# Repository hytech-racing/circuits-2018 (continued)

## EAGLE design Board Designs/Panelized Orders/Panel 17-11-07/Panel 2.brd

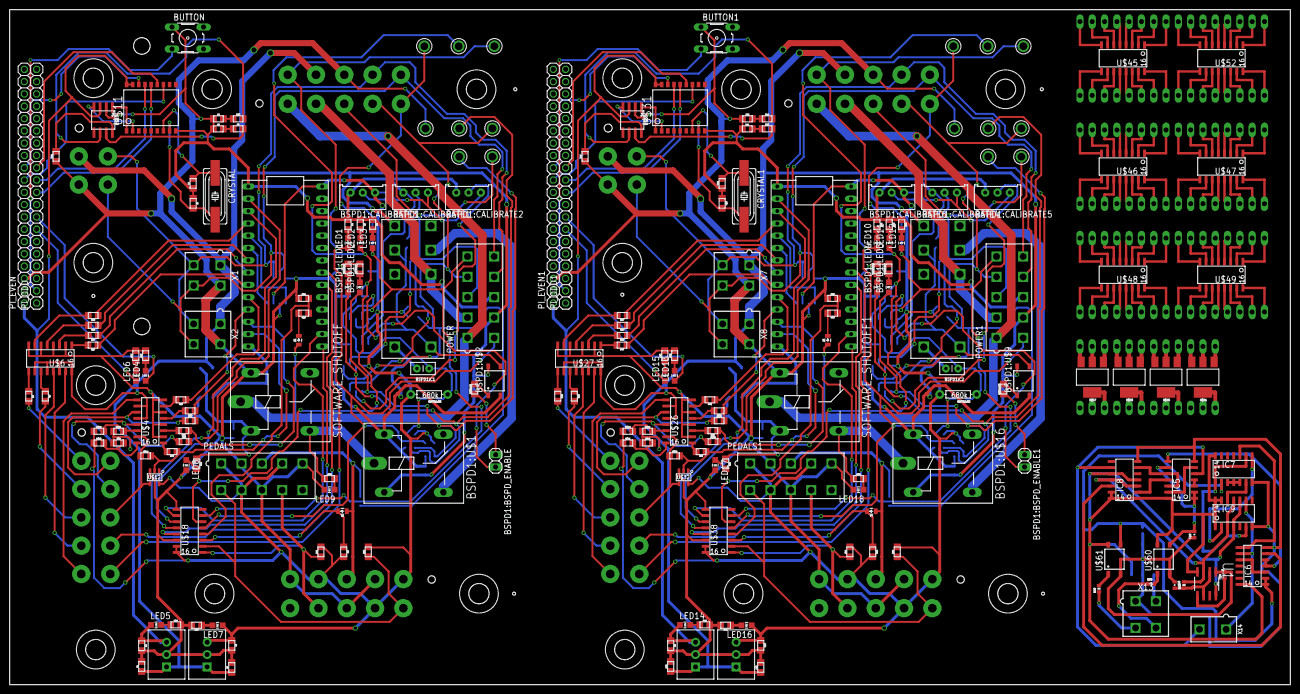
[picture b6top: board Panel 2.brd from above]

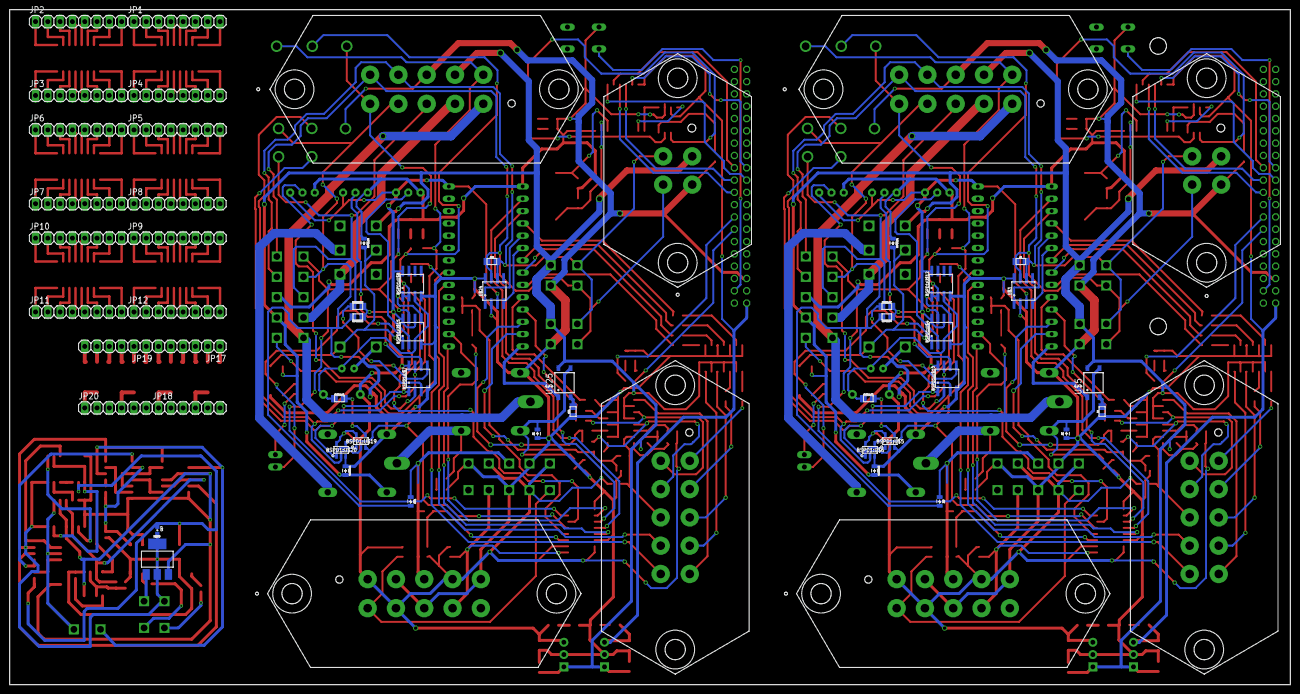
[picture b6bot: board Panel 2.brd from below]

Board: 2 copper layers, 264.4 x 139.4 mm, 270 parts (58 on the bottom side), 336 nets.

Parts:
BSPD1:BSPD_ENABLE, BSPD1:BSPD_ENABLE1: JUMPER; 1X02
BSPD1:C1, BSPD1:C2: .47u; CAP-PTH-SMALLEZ
BSPD1:CALIBRATE1, BSPD1:CALIBRATE2, BSPD1:CALIBRATE3, BSPD1:CALIBRATE4, BSPD1:CALIBRATE5, BSPD1:CALIBRATE6: TRIMPOT_3296
BSPD1:D1, BSPD1:D2, BSPD1:D3, BSPD1:D4: DIODE0805; 0805_D
BSPD1:LED1, BSPD1:LED4: RED; LED-805
BSPD1:LED2, BSPD1:LED3: YELLOW; LED-805
BSPD1:R1, BSPD1:R3: 330; 0805
BSPD1:R2, BSPD1:R5: 680k; AXIAL-0.3EZ
BSPD1:R4, BSPD1:R7, BSPD1:R11, BSPD1:R12: 10k; 0805
BSPD1:R6, BSPD1:R10: 680; 0805
BSPD1:R8, BSPD1:R9, BSPD1:R13, BSPD1:R14: 270; 0805
BSPD1:U$1, BSPD1:U$16: G5LE; ZF112
BSPD1:U$2, BSPD1:U$9: CPC1002N; SOP04
BSPD1:U$3, BSPD1:U$14: JW2SN-DC12V; JW2SN
BSPD1:U$4, BSPD1:U$7, BSPD1:U$10, BSPD1:U$15: MCP6542SOIC; SOIC-08
BSPD1:U$5, BSPD1:U$19: SN74AHC1G09; SOT-23-5
BSPD1:U$6, BSPD1:U$20: SN74LVC1G08; SOT-23-5
BSPD1:U$8, BSPD1:U$12: MCP6002SOIC; SOIC-08
BSPD1:U$11, BSPD1:U$13, BSPD1:U$17, BSPD1:U$18: TEST_POINT
BUTTON, BUTTON1: B3F-10XX
C1, C2, C5, C8, C9, C10, C15, C16: 10uF; 0805
C3, C4, C11, C12: 560pF; 0805
C6, C7, C13, C14: 22pF; 0805
C17, C18: 0402-CAP
C19, C20: 10nF; 0402-CAP
CRYSTAL, CRYSTAL1: 16MHz; HC49UP
D1, D2, D3, D4, D5, D6: DIODE0805; 0805_D
IC1, IC2, IC3, IC4: TO-220
IC5, IC6, IC7: SN74AHC00D; SOIC-14
IC8, IC9: SN74AHC74D; SOIC-14
JMP, JMP1: DIODE0805; 0805_D
JP1, JP2, JP3, JP4, JP5, JP6, JP7, JP8, JP9, JP10, JP11, JP12: 1X08
JP17, JP18, JP19, JP20: 1X06
LED1, LED6, LED8, LED9, LED10, LED15, LED17, LED18: RED; LED-805
LED2, LED11: YELLOW; LED-805
LED3, LED4, LED12, LED13: GREEN; LED-805
LED5, LED7, LED14, LED16: PURPLE; LED-805
PEDALS, PEDALS1: MINIFIT_5566-10
PI_EVEN, PI_EVEN1: 1X20
PI_ODD, PI_ODD1: 1X20
POWER, POWER1: MINIFIT_5566-10
R1, R30: 120; 0805
R2, R3, R15, R16, R17, R18, R19, R20, R21, R22, R27, R31, R32, R37, R38, R39, R40, R41, R42, R43, R44, R50: 270; 0805
R4, R25, R26, R28, R33, R48, R49, R51: 200; 0805
R5, R23, R45, R46: 100; 0805
R6, R34: 330; 0805
R7, R8, R52, R53: 0; 0805
R9, R10, R11, R54, R55, R56: 10k; 0805
R12, R29, R57, R58: 1.2K; 0805
R13, R35: 43k; 0805
R14, R36: 12k; 0805
R24, R47: 4.7k; 0805
R59, R60: 680Ω; 0402-RES
R61: 100kΩ; 0402-RES
SOFTWARE_SHUTOFF, SOFTWARE_SHUTOFF1: G5LE; ZF112
U1: SA555D; SOIC127P600X175-8N
U$1, U$23: TEENSY_3.2_SIMPLE
U$2, U$13, U$14, U$15, U$16, U$17, U$33, U$34, U$35, U$36, U$37, U$44: TEST_POINT
U$3, U$10, U$24, U$30: MCP2551; SOIC-08
U$4, U$6, U$26, U$27: TLP291-4; SOIC-16
U$5, U$25, U$60, U$61: CPC1002N; SOP04
U$7, U$8, U$9, U$19, U$20, U$21, U$22, U$28, U$29, U$39, U$40, U$41, U$42, U$43: JUMPER; 0805
U$11, U$31: MCP2515SMD; SOIC-18W
U$12, U$32: SN74LV1T34; SOT-23-5
U$18, U$38: MCP3208SOIC; SOIC-16
U$45, U$46, U$47, U$48, U$49, U$52: SOIC16; SOIC-16
U$50, U$51, U$57, U$58: SOT223
U$59: SOT223
X1, X2, X7, X8, X13: CONNECTOR-4; MINIFIT_5566-4
X3, X9: CONNECTOR-4MX150L_VERTICAL-4; MX150L_VERTICAL-4
X4, X5, X6, X10, X11, X12: CONNECTOR-10MX150L_VERTICAL-10; MX150L_VERTICAL-10
X14: CONNECTOR-2; MINIFIT_5566-2

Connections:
12V: U$59.1, X13.2
+5V: BSPD1:CALIBRATE1.1, BSPD1:CALIBRATE2.1, BSPD1:CALIBRATE3.1, BSPD1:R4.1, BSPD1:R5.P$2, BSPD1:R7.2, BSPD1:U$4.6, BSPD1:U$4.8, BSPD1:U$5.5, BSPD1:U$6.5, BSPD1:U$10.8, BSPD1:U$12.8, C8.1, IC3.3, LED7.A, PEDALS.1, PEDALS.4, PEDALS.7, R9.2, R10.2, R11.2, U$1.VIN, U$3.3, U$12.5, U$18.15, U$18.16, U$20.1, U$22.1, X4.1, X4.4, X4.7
+5V1: BSPD1:CALIBRATE4.1, BSPD1:CALIBRATE5.1, BSPD1:CALIBRATE6.1, BSPD1:R2.P$2, BSPD1:R11.1, BSPD1:R12.2, BSPD1:U$7.8, BSPD1:U$8.8, BSPD1:U$15.6, BSPD1:U$15.8, BSPD1:U$19.5, BSPD1:U$20.5, C16.1, IC4.3, LED16.A, PEDALS1.1, PEDALS1.4, PEDALS1.7, R54.2, R55.2, R56.2, U$23.VIN, U$24.3, U$32.5, U$38.15, U$38.16, U$41.1, U$43.1, X10.1, X10.4, X10.7
+5V2: IC5.14, IC6.14, IC7.14, IC8.1, IC8.4, IC8.10, IC8.13, IC8.14, IC9.1, IC9.4, IC9.10, IC9.13, IC9.14, U1.4, U1.8, U$59.3, U$60.4, U$61.4
+5V/1: C2.1, IC2.3, LED5.A, PI_EVEN.1, U$10.3, U$11.17, U$11.18
+5V/2: C9.1, IC1.3, LED14.A, PI_EVEN1.1, U$30.3, U$31.17, U$31.18
+12V: BSPD1:D2.C, BSPD1:U$1.2, BSPD1:U$2.4, BSPD1:U$3.4, C1.1, C5.1, IC2.1, IC3.1, POWER.7, U$4.10, U$4.12, U$5.4, U$6.10, U$6.12, U$6.14, U$6.16, U$9.1, U$21.1, X1.1, X2.1, X3.1, X5.7
+12V1: BSPD1:D4.C, BSPD1:U$9.4, BSPD1:U$14.4, BSPD1:U$16.2, C10.1, C15.1, IC1.1, IC4.1, POWER1.7, U$25.4, U$26.10, U$26.12, U$27.10, U$27.12, U$27.14, U$27.16, U$40.1, U$42.1, X7.1, X8.1, X9.1, X11.7
BMS_5V: C17.1, IC6.1, IC6.2, IC7.2, U$61.3
BMS_IN: R60.2, U$61.1
BMS_OUT: IC6.9, IC9.9, X14.1
BSPD1:N$1: BSPD1:D1.C, BSPD1:U$2.3, BSPD1:U$3.3, BSPD1:U$3.COIL-, BSPD1:U$4.5
BSPD1:N$2: BSPD1:R3.2, BSPD1:U$5.4
BSPD1:N$3: BSPD1:R6.2, BSPD1:U$2.1
BSPD1:N$4: BSPD1:BSPD_ENABLE.1, BSPD1:R6.1
BSPD1:N$5: BSPD1:CALIBRATE2.2, BSPD1:U$10.2
BSPD1:N$6: BSPD1:CALIBRATE1.2, BSPD1:U$10.6
BSPD1:N$7: BSPD1:CALIBRATE3.2, BSPD1:U$4.2
BSPD1:N$8: BSPD1:BSPD_ENABLE.2, BSPD1:U$4.1
BSPD1:N$9: BSPD1:C2.1, BSPD1:R1.1, BSPD1:R2.P$1, BSPD1:U$8.3, BSPD1:U$15.3
BSPD1:N$10: BSPD1:CALIBRATE6.2, BSPD1:U$15.2
BSPD1:N$11: BSPD1:D3.C, BSPD1:U$9.3, BSPD1:U$14.3, BSPD1:U$14.COIL-, BSPD1:U$15.5
BSPD1:N$12: BSPD1:R1.2, BSPD1:U$19.4
BSPD1:N$13: BSPD1:C1.1, BSPD1:R3.1, BSPD1:R5.P$1, BSPD1:U$4.3, BSPD1:U$12.3
BSPD1:N$14: BSPD1:LED2.C, BSPD1:R8.1
BSPD1:N$15: BSPD1:LED1.C, BSPD1:R9.1
BSPD1:N$16: BSPD1:LED1.A, BSPD1:U$5.2, BSPD1:U$6.2, BSPD1:U$10.7, BSPD1:U$11.P$1
BSPD1:N$17: BSPD1:LED2.A, BSPD1:U$5.1, BSPD1:U$6.1, BSPD1:U$10.1, BSPD1:U$13.P$1
BSPD1:N$18: BSPD1:R10.2, BSPD1:U$9.1
BSPD1:N$19: BSPD1:LED4.C, BSPD1:R14.1
BSPD1:N$20: BSPD1:LED3.C, BSPD1:R13.1
BSPD1:N$21: BSPD1:LED4.A, BSPD1:U$7.7, BSPD1:U$17.P$1, BSPD1:U$19.2, BSPD1:U$20.2
BSPD1:N$22: BSPD1:LED3.A, BSPD1:U$7.1, BSPD1:U$18.P$1, BSPD1:U$19.1, BSPD1:U$20.1
BSPD1:N$23: BSPD1:BSPD_ENABLE1.1, BSPD1:R10.1
BSPD1:N$24: BSPD1:BSPD_ENABLE1.2, BSPD1:U$15.1
BSPD1:N$25: BSPD1:CALIBRATE5.2, BSPD1:U$7.2
BSPD1:N$26: BSPD1:CALIBRATE4.2, BSPD1:U$7.6
BSPD1:SHUTDOWN_C: BSPD1:U$1.S, BSPD1:U$3.6
BSPD1:SHUTDOWN_C1: BSPD1:U$14.6, BSPD1:U$16.S
BUT: BUTTON.3, PI_ODD.2
BUT1: BUTTON1.3, PI_ODD1.2
CAN-H: R5.2, U$10.7
CAN-H1: R45.2, U$30.7
CAN-L: R23.2, U$10.6
CAN-L1: R46.2, U$30.6
CANH: POWER.10, R1.1, U$3.7, X1.4, X2.4, X3.4, X5.10
CANH1: POWER1.10, R30.1, U$24.7, X7.4, X8.4, X9.4, X11.10
CANL: POWER.9, R1.2, U$3.6, X1.3, X2.3, X3.3, X5.9
CANL1: POWER1.9, R30.2, U$24.6, X7.3, X8.3, X9.3, X11.9
CS: PI_EVEN.12, U$11.16
CS1: PI_EVEN1.12, U$31.16
DASH_CTRL1: R15.1, U$1.D2
DASH_CTRL2: R16.1, U$1.D5
DASH_CTRL3: R17.1, U$1.D6
DASH_CTRL4: R18.1, U$1.D7(RX3)
DASH_CTRL5: R19.1, U$1.D8(TX3)
DASH_CTRL6: R20.1, U$1.D9(RX2), U$7.2
DASH_CTRL7: R21.1, U$1.D10(TX2), U$8.2
DASH_CTRL8: R22.1, U$1.D11, U$12.2, U$19.2
DASH_CTRL9: U$1.A4, X6.9
DASH_CTRL10: U$1.A5, X6.10
DASH_CTRL11: R38.1, U$23.D5
DASH_CTRL12: R39.1, U$23.D6
DASH_CTRL13: R40.1, U$23.D7(RX3)
DASH_CTRL14: R42.1, U$23.D9(RX2), U$28.2
DASH_CTRL15: R44.1, U$23.D11, U$32.2, U$39.2
DASH_CTRL16: U$23.A5, X12.10
DASH_CTRL17: R37.1, U$23.D2
DASH_CTRL18: R41.1, U$23.D8(TX3)
DASH_CTRL19: R43.1, U$23.D10(TX2), U$29.2
DASH_CTRL20: U$23.A4, X12.9
DASH_IO1: R7.2, X6.1
DASH_IO2: R8.2, X6.2
DASH_IO3: U$6.13, X6.3
DASH_IO4: U$6.15, X6.4
DASH_IO5: U$4.9, X6.5
DASH_IO6: U$4.11, U$7.1, X6.6
DASH_IO7: U$4.13, U$8.1, X6.7
DASH_IO8: U$4.15, U$12.4, U$19.1, X6.8
DASH_IO9: R52.2, X12.1
DASH_IO10: R53.2, X12.2
DASH_IO11: U$27.13, X12.3
DASH_IO12: U$27.15, X12.4
DASH_IO13: U$26.9, X12.5
DASH_IO14: U$26.11, U$28.1, X12.6
DASH_IO15: U$26.13, U$29.1, X12.7
DASH_IO16: U$26.15, U$32.4, U$39.1, X12.8
GND: BSPD1:C1.2, BSPD1:CALIBRATE1.3, BSPD1:CALIBRATE2.3, BSPD1:CALIBRATE3.3, BSPD1:D1.A, BSPD1:D2.A, BSPD1:R8.2, BSPD1:R9.2, BSPD1:U$1.1, BSPD1:U$2.2, BSPD1:U$3.COIL+, BSPD1:U$4.4, BSPD1:U$5.3, BSPD1:U$6.3, BSPD1:U$10.4, BSPD1:U$12.4, BUTTON.1, C1.2, C2.2, C3.1, C4.1, C5.2, C6.1, C7.1, C8.2, D3.A, IC2.2, IC3.2, LED8.C, LED9.C, PEDALS.2, PEDALS.5, PEDALS.8, PI_EVEN.3, POWER.8, R2.1, R3.1, R4.1, R6.1, R14.1, R24.1, R25.2, R26.2, R27.2, R28.2, SOFTWARE_SHUTOFF.1, U$1.GND, U$2.P$1, U$3.2, U$3.8, U$4.2, U$4.4, U$4.6, U$4.8, U$6.2, U$6.4, U$6.6, U$6.8, U$10.2, U$11.9, U$12.3, U$18.9, U$18.14, X1.2, X2.2, X3.2, X4.2, X4.5, X4.8, X5.8
GND1: BSPD1:C2.2, BSPD1:CALIBRATE4.3, BSPD1:CALIBRATE5.3, BSPD1:CALIBRATE6.3, BSPD1:D3.A, BSPD1:D4.A, BSPD1:R13.2, BSPD1:R14.2, BSPD1:U$7.4, BSPD1:U$8.4, BSPD1:U$9.2, BSPD1:U$14.COIL+, BSPD1:U$15.4, BSPD1:U$16.1, BSPD1:U$19.3, BSPD1:U$20.3, BUTTON1.1, C9.2, C10.2, C11.1, C12.1, C13.1, C14.1, C15.2, C16.2, D6.A, IC1.2, IC4.2, LED17.C, LED18.C, PEDALS1.2, PEDALS1.5, PEDALS1.8, PI_EVEN1.3, POWER1.8, R31.1, R32.1, R33.1, R34.1, R36.1, R47.1, R48.2, R49.2, R50.2, R51.2, SOFTWARE_SHUTOFF1.1, U$23.GND, U$24.2, U$24.8, U$26.2, U$26.4, U$26.6, U$26.8, U$27.2, U$27.4, U$27.6, U$27.8, U$30.2, U$31.9, U$32.3, U$38.9, U$38.14, U$44.P$1, X7.2, X8.2, X9.2, X10.2, X10.5, X10.8, X11.8
GND2: C17.2, C18.1, C19.2, C20.1, IC5.7, IC6.7, IC7.7, IC8.7, IC9.7, U1.1, U$59.2, U$59.4, U$60.2, U$61.2, X13.1
IMD_5V: C18.2, IC5.1, IC5.2, IC5.9, U$60.3
IMD_IN: R59.2, U$60.1
IMD_OUT: IC5.5, IC8.9, X14.2
INT: PI_EVEN.11, U$11.12
INT1: PI_EVEN1.11, U$31.12
LED1: LED4.A, PI_ODD.8
LED2: LED6.A, PI_ODD.7
LED3: LED15.A, PI_ODD1.7
LED4: LED13.A, PI_ODD1.8
MCP3208_CS: U$1.A0, U$18.10
MCP3208_CS1: U$23.A0, U$38.10
MCP3208_DIN: U$1.D1(TX1), U$18.11
MCP3208_DIN1: U$23.D1(TX1), U$38.11
MCP3208_DOUT: U$1.D0(RX1), U$18.12
MCP3208_DOUT1: U$23.D0(RX1), U$38.12
MCP3208_SCK: U$1.D13, U$18.13
MCP3208_SCK1: U$23.D13, U$38.13
MISO: PI_ODD.11, U$11.15
MISO1: PI_ODD1.11, U$31.15
MOSI: PI_ODD.10, U$11.14
MOSI1: PI_ODD1.10, U$31.14
unnamed: R7.1, U$6.9
unnamed: U$1.D4(CANRX), U$3.4
unnamed: R8.1, U$6.11
unnamed: U$4.16, U$9.2, U$20.2
unnamed: U$1.D3(CANTX), U$3.1
unnamed: U$4.14, U$21.2, U$22.2
unnamed: D1.C, R9.1, U$18.3
unnamed: LED8.A, R12.2
unnamed: LED9.A, R29.2
unnamed: U$23.D4(CANRX), U$24.4
unnamed: U$23.D3(CANTX), U$24.1
unnamed: D3.C, R12.1, SOFTWARE_SHUTOFF.2, U$5.3
unnamed: D2.C, R13.2
unnamed: LED1.C, R2.2
unnamed: LED2.C, R3.2
unnamed: LED3.C, R4.2
unnamed: LED10.C, R31.2
unnamed: LED11.C, R32.2
unnamed: R15.2, U$6.7
unnamed: LED12.C, R33.2
unnamed: R34.2, U$25.2
unnamed: R6.2, U$5.2
unnamed: D4.C, R54.1, U$38.3
unnamed: R16.2, U$6.5
unnamed: D6.C, R57.1, SOFTWARE_SHUTOFF1.2, U$25.3
unnamed: D5.C, R35.2
unnamed: R21.2, U$4.3
unnamed: R17.2, U$6.3
unnamed: R18.2, U$6.1
unnamed: R37.2, U$27.7
unnamed: R19.2, U$4.7
unnamed: R20.2, U$4.5
unnamed: R38.2, U$27.5
unnamed: R39.2, U$27.3
unnamed: R22.2, U$4.1
unnamed: R40.2, U$27.1
unnamed: U$10.1, U$11.1
unnamed: R41.2, U$26.7
unnamed: U$10.4, U$11.2
unnamed: C6.2, CRYSTAL.2, U$11.8
unnamed: R24.2, U$10.8
unnamed: C7.2, CRYSTAL.1, U$11.7
unnamed: C3.2, R5.1
unnamed: R42.2, U$26.5
unnamed: R43.2, U$26.3
unnamed: R44.2, U$26.1
unnamed: U$30.1, U$31.1
unnamed: U$30.4, U$31.2
unnamed: C13.2, CRYSTAL1.2, U$31.8
unnamed: C4.2, R23.1
unnamed: R47.2, U$30.8
unnamed: LED4.C, R25.1
unnamed: LED5.C, R26.1
unnamed: LED6.C, R27.1
unnamed: LED7.C, R28.1
unnamed: C14.2, CRYSTAL1.1, U$31.7
unnamed: C11.2, R45.1
unnamed: C12.2, R46.1
unnamed: LED13.C, R48.1
unnamed: LED14.C, R49.1
unnamed: LED15.C, R50.1
unnamed: LED16.C, R51.1
unnamed: R52.1, U$27.9
unnamed: R53.1, U$27.11
unnamed: U$26.16, U$40.2, U$41.2
unnamed: U$26.14, U$42.2, U$43.2
unnamed: LED17.A, R57.2
unnamed: LED18.A, R58.2
unnamed: JP1.1, U$45.1
unnamed: JP1.2, U$45.2
unnamed: JP1.3, U$45.3
unnamed: JP1.4, U$45.4
unnamed: JP1.5, U$45.5
unnamed: JP1.6, U$45.6
unnamed: JP1.7, U$45.7
unnamed: JP1.8, U$45.8
unnamed: JP2.1, U$52.1
unnamed: JP2.2, U$52.2
unnamed: JP2.3, U$52.3
unnamed: JP2.4, U$52.4
unnamed: JP2.5, U$52.5
unnamed: JP2.6, U$52.6
unnamed: JP2.7, U$52.7
unnamed: JP2.8, U$52.8
unnamed: JP3.1, U$52.16
unnamed: JP3.2, U$52.15
unnamed: JP3.3, U$52.14
unnamed: JP3.4, U$52.13
unnamed: JP3.5, U$52.12
unnamed: JP3.6, U$52.11
unnamed: JP3.7, U$52.10
unnamed: JP3.8, U$52.9
unnamed: JP4.1, U$45.16
unnamed: JP4.2, U$45.15
unnamed: JP4.3, U$45.14
unnamed: JP4.4, U$45.13
unnamed: JP4.5, U$45.12
unnamed: JP4.6, U$45.11
unnamed: JP4.7, U$45.10
unnamed: JP4.8, U$45.9
unnamed: JP5.1, U$46.1
unnamed: JP5.2, U$46.2
unnamed: JP5.3, U$46.3
unnamed: JP5.4, U$46.4
unnamed: JP5.5, U$46.5
unnamed: JP5.6, U$46.6
unnamed: JP5.7, U$46.7
unnamed: JP5.8, U$46.8
unnamed: JP6.1, U$47.1
unnamed: JP6.2, U$47.2
unnamed: JP6.3, U$47.3
unnamed: JP6.4, U$47.4
unnamed: JP6.5, U$47.5
unnamed: JP6.6, U$47.6
unnamed: JP6.7, U$47.7
unnamed: JP6.8, U$47.8
unnamed: JP7.1, U$47.16
unnamed: JP7.2, U$47.15
unnamed: JP7.3, U$47.14
unnamed: JP7.4, U$47.13
unnamed: JP7.5, U$47.12
unnamed: JP7.6, U$47.11
unnamed: JP7.7, U$47.10
unnamed: JP7.8, U$47.9
unnamed: JP8.1, U$46.16
unnamed: JP8.2, U$46.15
unnamed: JP8.3, U$46.14
unnamed: JP8.4, U$46.13
unnamed: JP8.5, U$46.12
unnamed: JP8.6, U$46.11
unnamed: JP8.7, U$46.10
unnamed: JP8.8, U$46.9
unnamed: JP9.1, U$48.1
unnamed: JP9.2, U$48.2
unnamed: JP9.3, U$48.3
unnamed: JP9.4, U$48.4
unnamed: JP9.5, U$48.5
unnamed: JP9.6, U$48.6
unnamed: JP9.7, U$48.7
unnamed: JP9.8, U$48.8
unnamed: JP10.1, U$49.1
unnamed: JP10.2, U$49.2
unnamed: JP10.3, U$49.3
unnamed: JP10.4, U$49.4
unnamed: JP10.5, U$49.5
unnamed: JP10.6, U$49.6
unnamed: JP10.7, U$49.7
unnamed: JP10.8, U$49.8
unnamed: JP11.1, U$49.16
unnamed: JP11.2, U$49.15
unnamed: JP11.3, U$49.14
unnamed: JP11.4, U$49.13
unnamed: JP11.5, U$49.12
unnamed: JP11.6, U$49.11
unnamed: JP11.7, U$49.10
unnamed: JP11.8, U$49.9
unnamed: JP12.1, U$48.16
unnamed: JP12.2, U$48.15
unnamed: JP12.3, U$48.14
unnamed: JP12.4, U$48.13
unnamed: JP12.5, U$48.12
unnamed: JP12.6, U$48.11
unnamed: JP12.7, U$48.10
unnamed: JP12.8, U$48.9
unnamed: JP18.1, U$50.4
unnamed: JP17.6, U$50.1
unnamed: JP17.5, U$50.2
unnamed: JP17.4, U$50.3
unnamed: JP17.3, U$57.1
unnamed: JP17.2, U$57.2
unnamed: JP17.1, U$57.3
unnamed: JP18.4, U$57.4
unnamed: JP20.1, U$51.4
unnamed: JP20.4, U$58.4
unnamed: JP19.6, U$51.1
unnamed: JP19.5, U$51.2
unnamed: JP19.4, U$51.3
unnamed: JP19.3, U$58.1
unnamed: JP19.2, U$58.2
unnamed: JP19.1, U$58.3
unnamed: IC5.10, IC5.12, IC8.6
unnamed: IC5.11, IC8.2
unnamed: IC7.1, IC7.9, IC9.6
unnamed: IC7.8, IC9.2
unnamed: IC6.6, IC8.12
unnamed: IC7.6, IC9.12
unnamed: R59.1, X13.4
unnamed: R60.1, X13.3
unnamed: IC5.3, IC5.4
unnamed: IC5.6, IC5.13
unnamed: IC5.8, IC6.4, IC6.5
unnamed: IC6.3, IC6.10
unnamed: IC6.8, IC7.10
unnamed: IC7.3, IC7.4, IC7.5
unnamed: IC8.3, IC8.11, IC9.3, IC9.11, R61.2, U1.3
unnamed: C20.2, R61.1, U1.2, U1.6
unnamed: C19.1, U1.5
RAW_ACCEL1: PEDALS.9, R11.1, U$18.1, X4.9
RAW_ACCEL2: PEDALS.6, R10.1, U$18.2, X4.6
RAW_ACCEL3: PEDALS1.6, R55.1, U$38.2, X10.6
RAW_ACCEL4: PEDALS1.9, R56.1, U$38.1, X10.9
RAW_BRAKE: D1.A, JMP.A, PEDALS.3, X4.3
RAW_BRAKE1: D4.A, JMP1.A, PEDALS1.3, X10.3
READ_CHARGE: BSPD1:U$12.1, BSPD1:U$12.2, LED2.A, U$16.P$1, U$18.6
READ_CHARGE1: BSPD1:U$8.1, BSPD1:U$8.2, LED11.A, U$36.P$1, U$38.6
READ_FAULT: BSPD1:U$4.7, LED3.A, POWER.5, U$15.P$1, U$18.7, X5.5
READ_FAULT1: BSPD1:U$15.7, LED12.A, POWER1.5, U$35.P$1, U$38.7, X11.5
READ_SWITCH: BSPD1:U$6.4, LED1.A, POWER.6, U$17.P$1, U$18.5, X5.6
READ_SWITCH1: BSPD1:U$20.4, LED10.A, POWER1.6, U$37.P$1, U$38.5, X11.6
READ_UPSTREAM_SHUTDOWN: R13.1, R14.2, U$18.4
READ_UPSTREAM_SHUTDOWN1: R35.1, R36.2, U$38.4
SCK: PI_ODD.12, U$11.13
SCK1: PI_ODD1.12, U$31.13
SHUTDOWN_A: D2.A, POWER.1, SOFTWARE_SHUTOFF.P, X5.1
SHUTDOWN_A1: D5.A, POWER1.1, SOFTWARE_SHUTOFF1.P, X11.1
SHUTDOWN_B: BSPD1:U$1.P, R29.1, SOFTWARE_SHUTOFF.S
SHUTDOWN_B1: BSPD1:U$16.P, R58.1, SOFTWARE_SHUTOFF1.S
SHUTDOWN_D: BSPD1:U$3.7, POWER.2, X5.2
SHUTDOWN_D1: BSPD1:U$14.7, POWER1.2, X11.2
SHUTDOWN_RELAY_CTRL: U$1.D12, U$5.1
SHUTDOWN_RELAY_CTRL1: U$23.D12, U$25.1
SIGNAL_BRAKE: BSPD1:R4.2, BSPD1:U$10.5, JMP.C, POWER.4, U$13.P$1, X5.4
SIGNAL_BRAKE1: BSPD1:R11.2, BSPD1:U$7.5, JMP1.C, POWER1.4, U$33.P$1, X11.4
SIGNAL_CURRENT: BSPD1:R7.1, BSPD1:U$10.3, POWER.3, U$14.P$1, X5.3
SIGNAL_CURRENT1: BSPD1:R12.1, BSPD1:U$7.3, POWER1.3, U$34.P$1, X11.3

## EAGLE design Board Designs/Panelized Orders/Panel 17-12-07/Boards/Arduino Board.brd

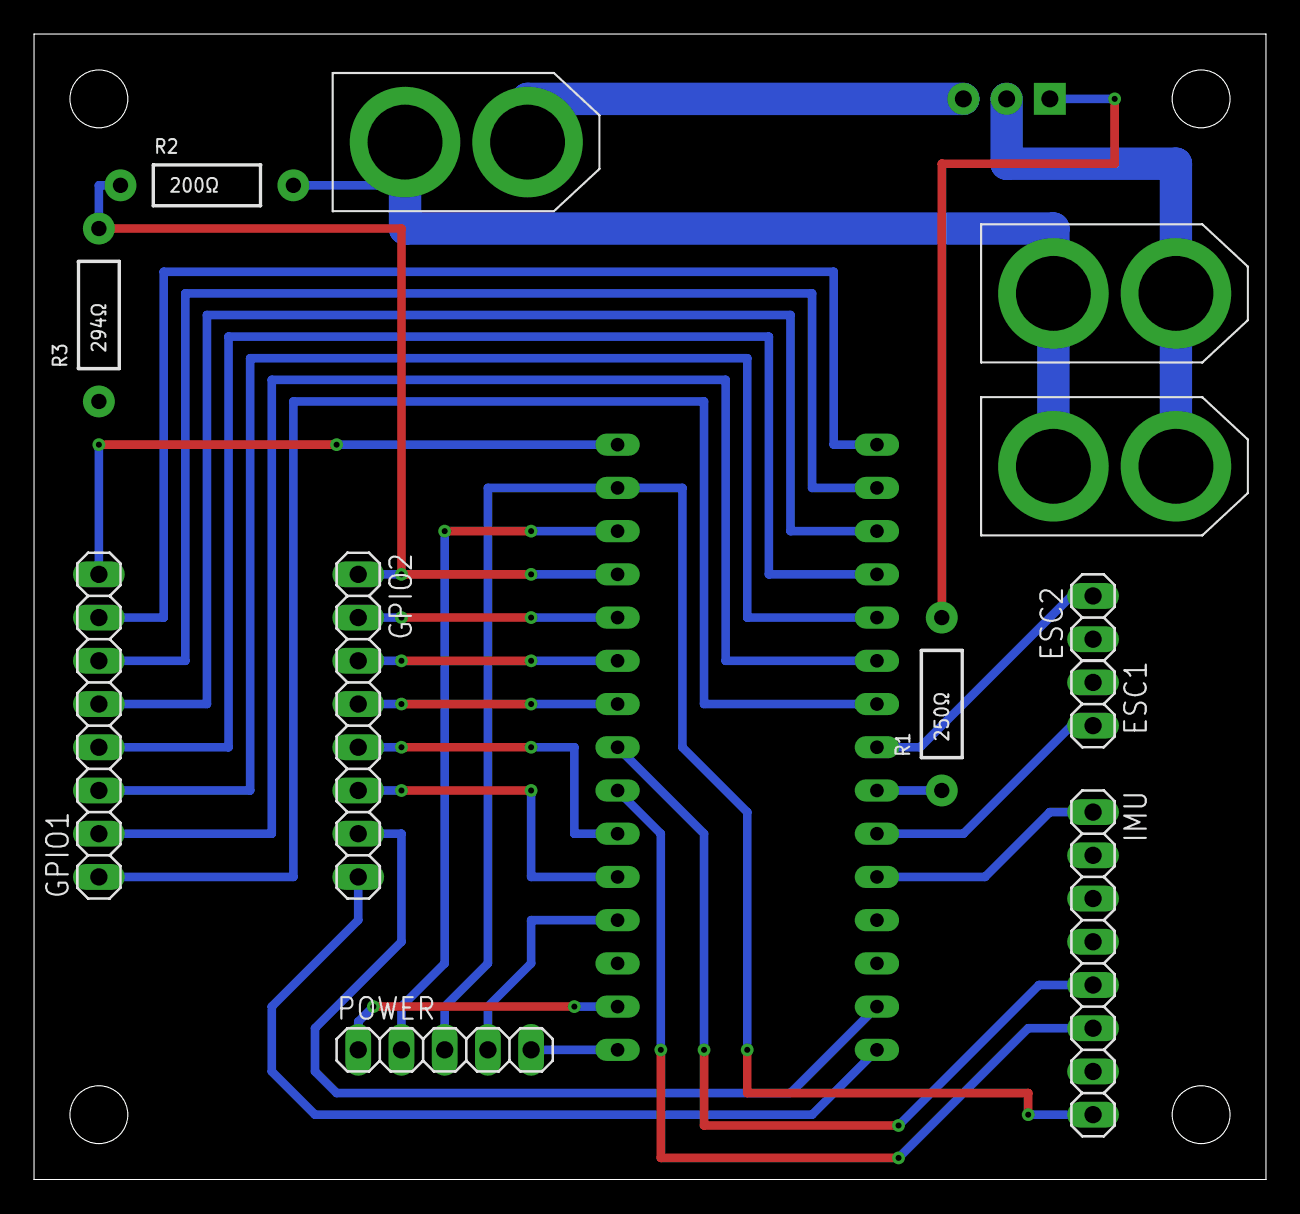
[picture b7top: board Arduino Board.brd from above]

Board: 2 copper layers, 72.4 x 67.3 mm, 14 parts (1 on the bottom side), 30 nets.

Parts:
BATTERY_POWER: XT60
ESC1, ESC2: M02; 1X02
ESC1_POWER, ESC2_POWER: XT60
GPIO1, GPIO2: 1X08
IMU: 1X08
POWER: 1X05
POWER_MOSFET: TO-220-SINK
R1: 250Ω; AXIAL-0.4
R2: 200Ω; AXIAL-0.4
R3: 294Ω; AXIAL-0.4
U$1: ARDUINO_NANO

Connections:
3.3V: IMU.8, POWER.3, U$1.3.3V
5V: POWER.4, U$1.5V
A0: GPIO2.1, R2.P$1, R3.P$2, U$1.A0
A1: GPIO2.2, U$1.A1
A2: GPIO2.3, U$1.A2
A3: GPIO2.4, U$1.A3
A6: GPIO2.5, U$1.A6
A7: GPIO2.6, U$1.A7
AREF: POWER.2, U$1.AREF
D0(RX): GPIO2.7, U$1.D0(RX)
D1(TX): GPIO2.8, U$1.D1(TX)
D6: GPIO1.1, U$1.D6
D7: GPIO1.2, U$1.D7
D8: GPIO1.3, U$1.D8
D9: GPIO1.4, U$1.D9
D10: GPIO1.5, U$1.D10
D11: GPIO1.6, U$1.D11
D12: GPIO1.7, U$1.D12
D13: GPIO1.8, U$1.D13
DRIVE: R1.P$1, U$1.D4
ESC1: ESC1.2, U$1.D3
ESC2: ESC2.2, U$1.D5
GND: BATTERY_POWER.-, ESC1.1, ESC2.1, IMU.7, POWER.1, POWER_MOSFET.3, R3.P$1, U$1.GND, U$1.GND1
INT: IMU.1, U$1.D2
unnamed: POWER_MOSFET.1, R1.P$2
SCL: IMU.6, U$1.A5
SDA: IMU.5, U$1.A4
SUPPLY+: BATTERY_POWER.+, ESC1_POWER.+, ESC2_POWER.+, R2.P$2
SUPPLY-: ESC1_POWER.-, ESC2_POWER.-, POWER_MOSFET.2
VIN: POWER.5, U$1.VIN

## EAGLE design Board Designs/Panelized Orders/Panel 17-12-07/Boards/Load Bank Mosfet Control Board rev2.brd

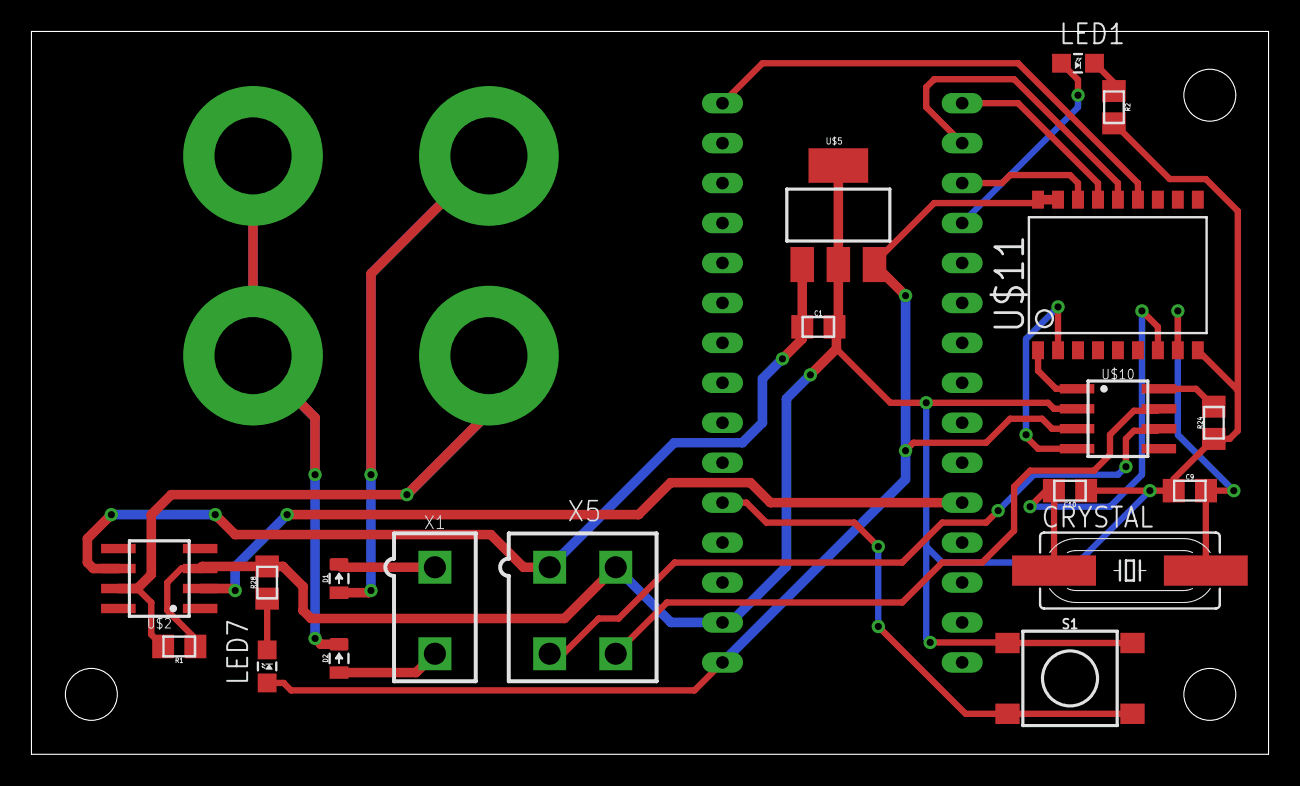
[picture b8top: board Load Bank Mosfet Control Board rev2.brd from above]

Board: 2 copper layers, 78.7 x 46.0 mm, 21 parts (1 on the bottom side), 24 nets.

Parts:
C1: .22uF; 0805
C9, C10: 22pF; 0805
CRYSTAL: 16MHz; HC49UP
D1, D2: DIODE0805; 0805_D
LED1: GREEN; LED-805
LED7: PURPLE; LED-805
R1: 10k; 0805
R2, R28: 200; 0805
R24: 4.7k; 0805
S1: TACTILE_SWITCH_SMD_6.2MM_TALL
U$2: MC34152; SOIC-08
U$3: IXTN660N04T4; SOT-227B
U$4: ARDUINO_NANO
U$5: SOT223
U$10: MCP2551; SOIC-08
U$11: MCP2515SMD; SOIC-18W
X1: CONNECTOR-2; MINIFIT_5566-2
X5: MINIFIT_5566-4

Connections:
+5V: LED7.A, U$4.VIN, U$5.3, U$10.3, U$11.17, U$11.18
+12V: C1.1, U$2.6, U$5.1, X5.1
CANH: U$10.7, X5.4
CANL: U$10.6, X5.3
CS: U$4.D10, U$11.16
GND: C1.2, C9.1, C10.1, R1.1, R2.2, R24.1, R28.2, S1.B1, S1.B2, U$2.3, U$4.GND, U$5.2, U$5.4, U$10.2, U$11.9, X5.2
MISO: U$4.D12, U$11.15
MOSI: U$4.D11, U$11.14
unnamed: D1.C, X1.1
unnamed: D1.A, U$3.P$1
unnamed: R1.2, U$2.7, U$3.P$4
unnamed: U$2.2, U$4.D2
unnamed: D2.C, U$3.P$2, U$3.P$3
unnamed: LED1.A, U$4.D9
unnamed: D2.A, X1.2
unnamed: LED1.C, R2.1
unnamed: S1.A1, S1.A2, U$4.A7
unnamed: U$10.1, U$11.1
unnamed: U$10.4, U$11.2
unnamed: C9.2, CRYSTAL.2, U$11.8
unnamed: R24.2, U$10.8
unnamed: C10.2, CRYSTAL.1, U$11.7
unnamed: LED7.C, R28.1
SCK: U$4.D13, U$11.13
